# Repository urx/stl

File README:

STL - Sequential Tail Lights
============================

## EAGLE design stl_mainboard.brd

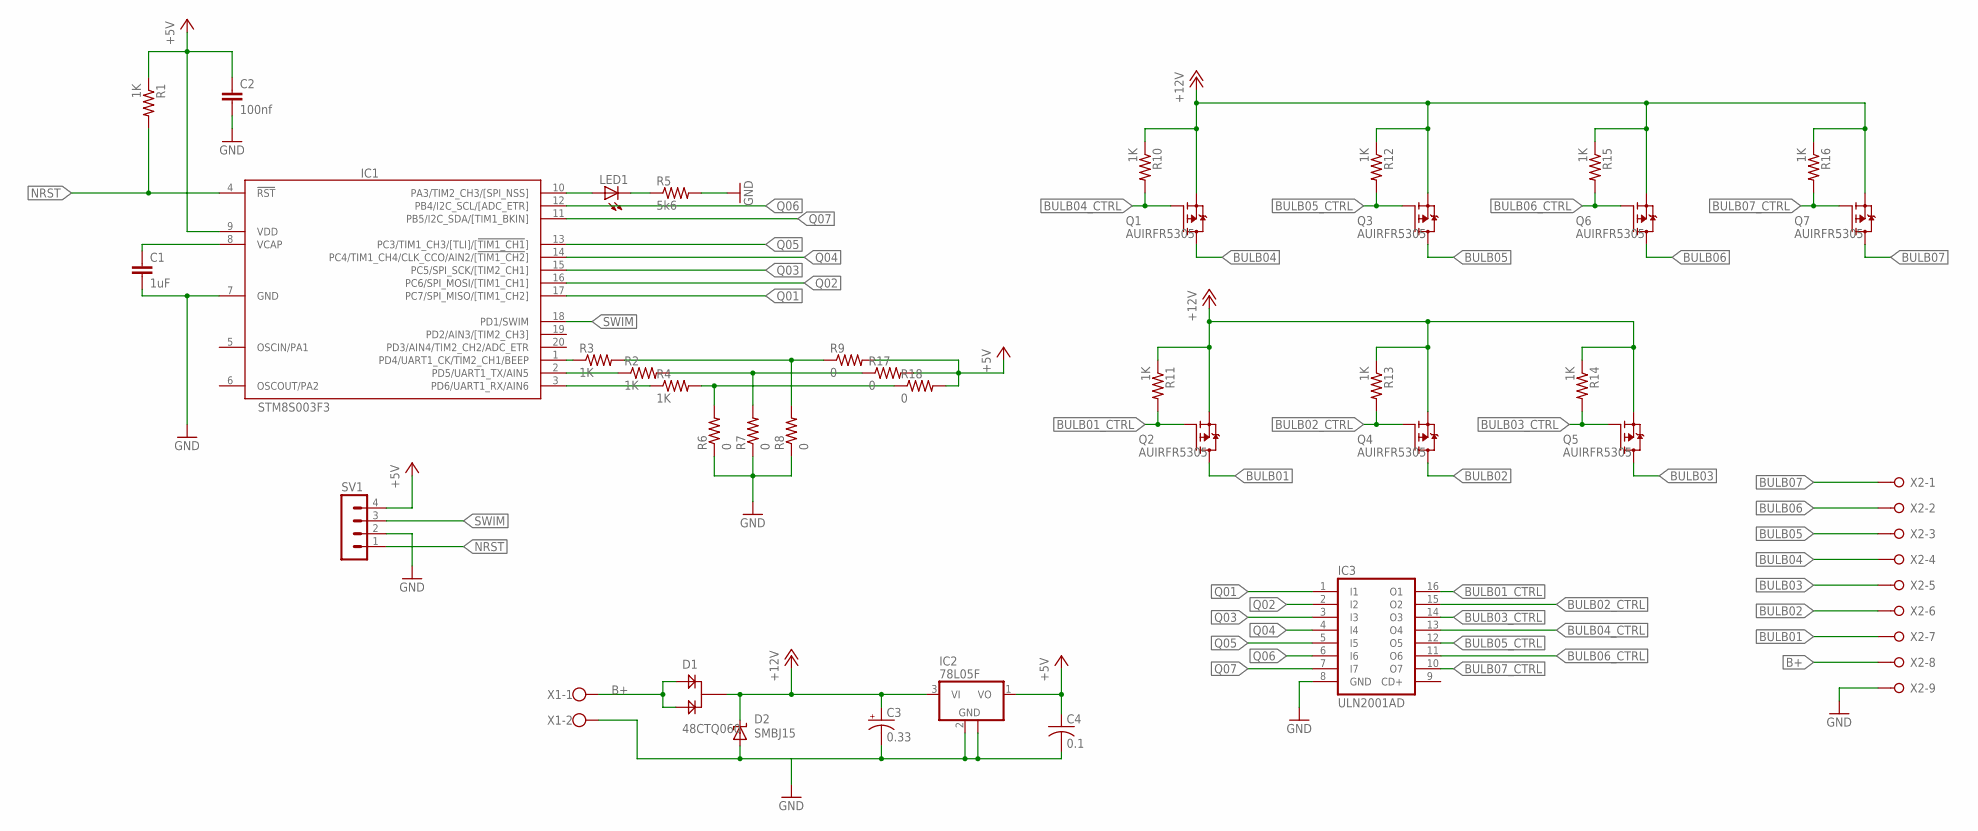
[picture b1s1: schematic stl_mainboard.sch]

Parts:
C1: 1uF; C1206
C2: 100nf; C1206
C3: 0.33; E5-8,5
C4: 0.1; C0805
D1: 48CTQ060; TO263AB
D2: SMBJ15; SMBJ
IC1: STM8S003F3; TSSOP20
IC2: 78L05F; SOT89
IC3: ULN2001AD; SO16
LED1: LEDSML1206; SML1206
Q1, Q2, Q3, Q4, Q5, Q6, Q7: AUIRFR5305; TO252
R1, R2, R3, R4, R10, R11, R12, R13, R14, R15, R16: 1K; M0805
R5: 5k6; M0805
R6, R7, R8, R9, R17, R18: 0; M0805
SV1: MA04-1
X1: W237-102
X2: W237-09P; W237-9P

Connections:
+5V: C2.1, C4.1, IC1.9 (VDD), IC2.1 (VO), R1.1, R9.2, R17.2, R18.2, SV1.4
B+: D1.1, D1.2, X1.1, X2.8
BULB01: Q2.3 (D), X2.7
BULB01_CTRL: IC3.16 (O1), Q2.1 (G), R11.2
BULB02: Q4.3 (D), X2.6
BULB02_CTRL: IC3.15 (O2), Q4.1 (G), R13.2
BULB03: Q5.3 (D), X2.5
BULB03_CTRL: IC3.14 (O3), Q5.1 (G), R14.2
BULB04: Q1.3 (D), X2.4
BULB04_CTRL: IC3.13 (O4), Q1.1 (G), R10.2
BULB05: Q3.3 (D), X2.3
BULB05_CTRL: IC3.12 (O5), Q3.1 (G), R12.2
BULB06: Q6.3 (D), X2.2
BULB06_CTRL: IC3.11 (O6), Q6.1 (G), R15.2
BULB07: Q7.3 (D), X2.1
BULB07_CTRL: IC3.10 (O7), Q7.1 (G), R16.2
GND: C1.2, C2.2, C3.-, C4.2, D2.A, IC1.7 (GND), IC2.2 (GND), IC2.2@1 (GND), IC3.8 (GND), R5.2, R6.1, R7.1, R8.1, SV1.2, X1.2, X2.9
unnamed: IC1.10 (PA3/TIM2_CH3/[SPI_NSS]), LED1.A
unnamed: LED1.C, R5.1
unnamed: C1.1, IC1.8 (VCAP)
unnamed: IC1.1 (PD4/UART1_CK/TIM2_CH1/BEEP), R3.1
unnamed: IC1.2 (PD5/UART1_TX/AIN5), R2.1
unnamed: IC1.3 (PD6/UART1_RX/AIN6), R4.1
unnamed: R3.2, R8.2, R9.1
unnamed: R2.2, R7.2, R17.1
unnamed: R4.2, R6.2, R18.1
NRST: IC1.4 (!RST), R1.2, SV1.1
Q01: IC1.17 (PC7/SPI_MISO/[TIM1_CH2]), IC3.1 (I1)
Q02: IC1.16 (PC6/SPI_MOSI/[TIM1_CH1]), IC3.2 (I2)
Q03: IC1.15 (PC5/SPI_SCK/[TIM2_CH1]), IC3.3 (I3)
Q04: IC1.14 (PC4/TIM1_CH4/CLK_CCO/AIN2/[!TIM1_CH2!]), IC3.4 (I4)
Q05: IC1.13 (PC3/TIM1_CH3/[TLI]/[!TIM1_CH1!]), IC3.5 (I5)
Q06: IC1.12 (PB4/I2C_SCL/[ADC_ETR]), IC3.6 (I6)
Q07: IC1.11 (PB5/I2C_SDA/[TIM1_BKIN]), IC3.7 (I7)
SWIM: IC1.18 (PD1/SWIM), SV1.3
VDD: C3.+, D1.K, D2.C, IC2.3 (VI), Q1.2 (S), Q2.2 (S), Q3.2 (S), Q4.2 (S), Q5.2 (S), Q6.2 (S), Q7.2 (S), R10.1, R11.1, R12.1, R13.1, R14.1, R15.1, R16.1

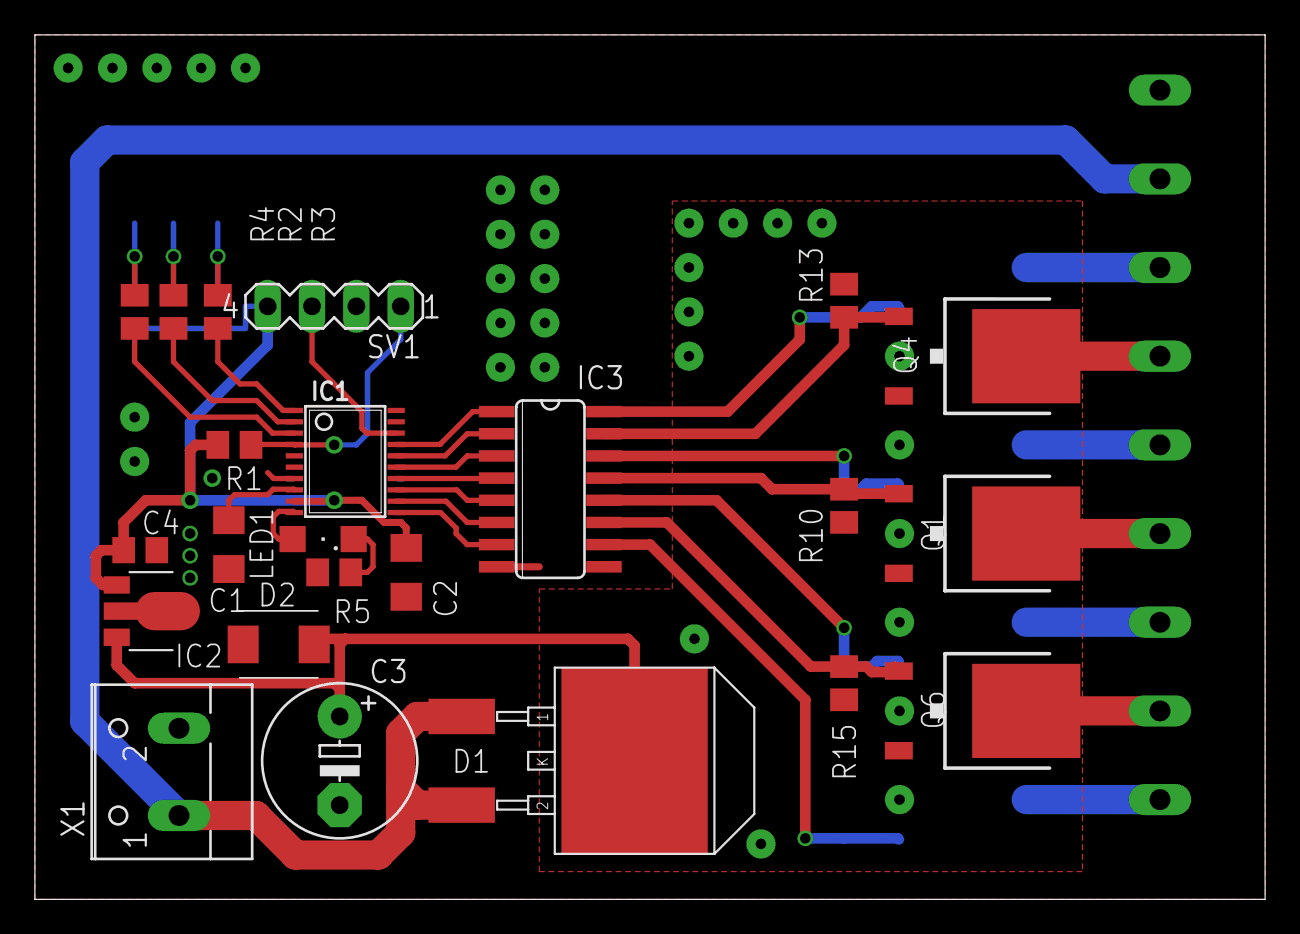
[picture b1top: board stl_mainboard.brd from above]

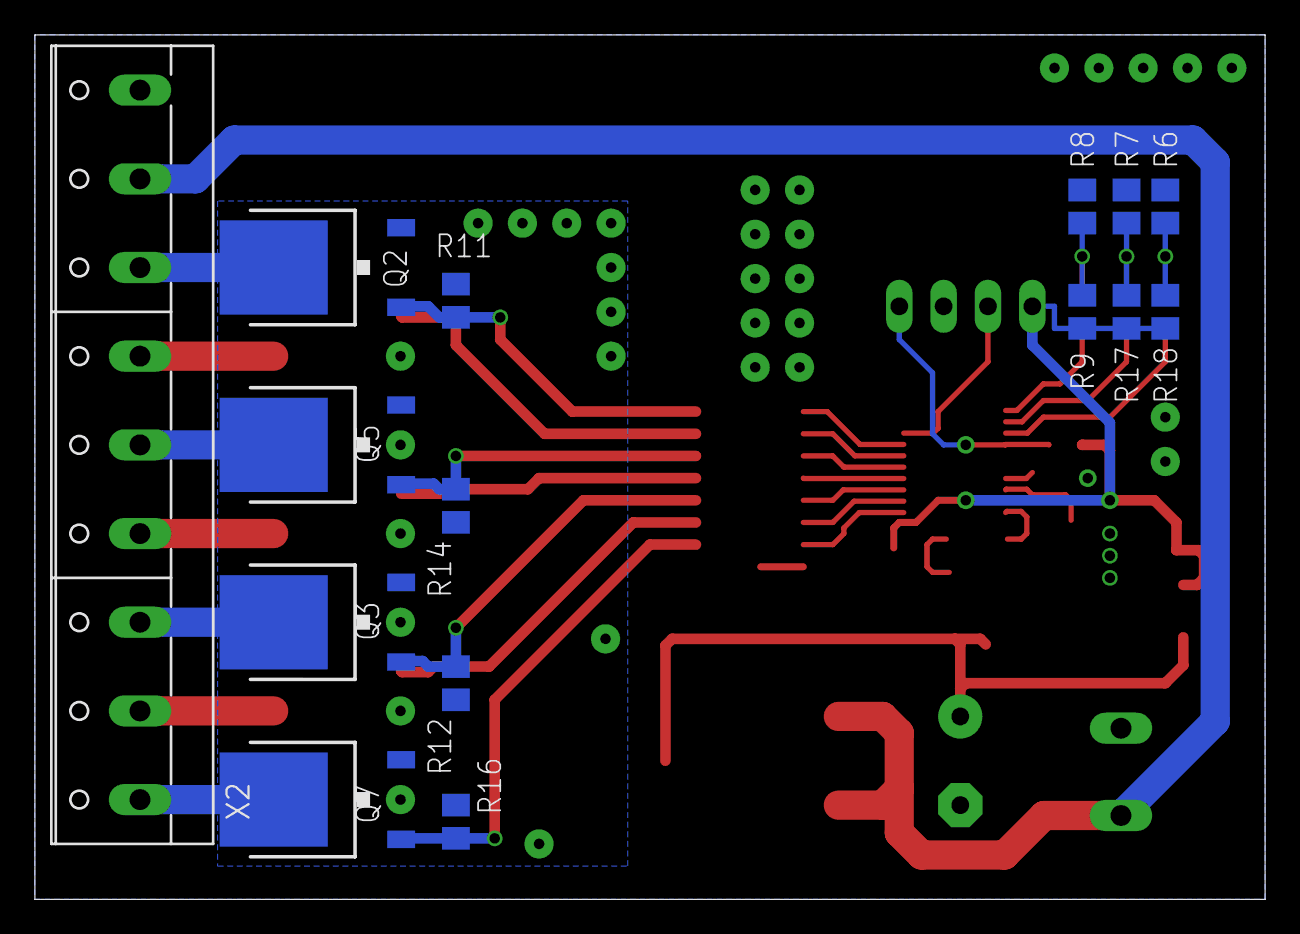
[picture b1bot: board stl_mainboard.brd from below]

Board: 2 copper layers, 70.5 x 49.5 mm, 38 parts (15 on the bottom side), 36 nets.

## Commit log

2017-04-10 adds .gitignore file
2017-04-10 Adds basicaly 555 timer schematic for 300ms period
    TODO:
    * develop CD4017 counter schematic with jumper based scaling
    * develop 5V power supply
    * develop revers voltage protection
    * develop fuse
    * develop antistatic protection
2017-04-11 Adds basicaly 555 timer schematic for 300ms period TODO: * develop 5V power supply * develop revers voltage protection * develop fuse * develop antistatic protection * develop MOSFET-base load control
2017-04-11 Adds power mosfets, removes unnecessary 7805 TODO: * develop revers voltage protection * develop fuse * develop antistatic protection
2017-04-12 WIP: input voltage spike and reverse protection
    Also adds wago 508 screw connectors
    TODO:
    * develop fuse
    * develop antistatic protection
2017-04-13 mainboard in progress
2017-04-14 board and schematics done
2017-04-17 improve routing power polygones
2017-07-28 No more 555 and 4017. STM8 instead.
2017-08-02 Added 'LEARN' jumper
2017-09-19 all schematics related stuff moved into hw directory
2017-09-19 Initial commit of firmware. led blinker now
2017-09-19 improve readme :)
2018-02-09 switched to stm8spl.lib
2018-02-12 .gitignore added
2018-02-12 build on Darwin host
2018-02-12 removed trash code
2018-02-12 partially working, need to be tested
2018-02-12 it blinks. TODO: * fist TIM2 interrupts fires up immediatelly * implement learn procedure
2018-05-07 temporary disable learning by ifdef
2019-05-21 MISC: adds stm8spl as submodule
2019-05-21 update stm8spl head
2019-05-24 wip: build system
2019-05-28 sublime stuff
2019-05-28 MISC: clean *.adb files
2019-10-18 proper submodule for stm8spl
2019-12-07 MISC: schematic in kicad
2019-12-08 WIP: tracing in progress
2019-12-12 WIP: draft tracing
2020-01-08 cosmetic changes
2020-01-10 [FEAT]: pcb is traced, v2.0
2020-01-10 [FEAT]: resistors R1-R4 moved together
2020-01-10 [FEAT]: edited missed via
2020-01-15 Some writings, adds gerbers
